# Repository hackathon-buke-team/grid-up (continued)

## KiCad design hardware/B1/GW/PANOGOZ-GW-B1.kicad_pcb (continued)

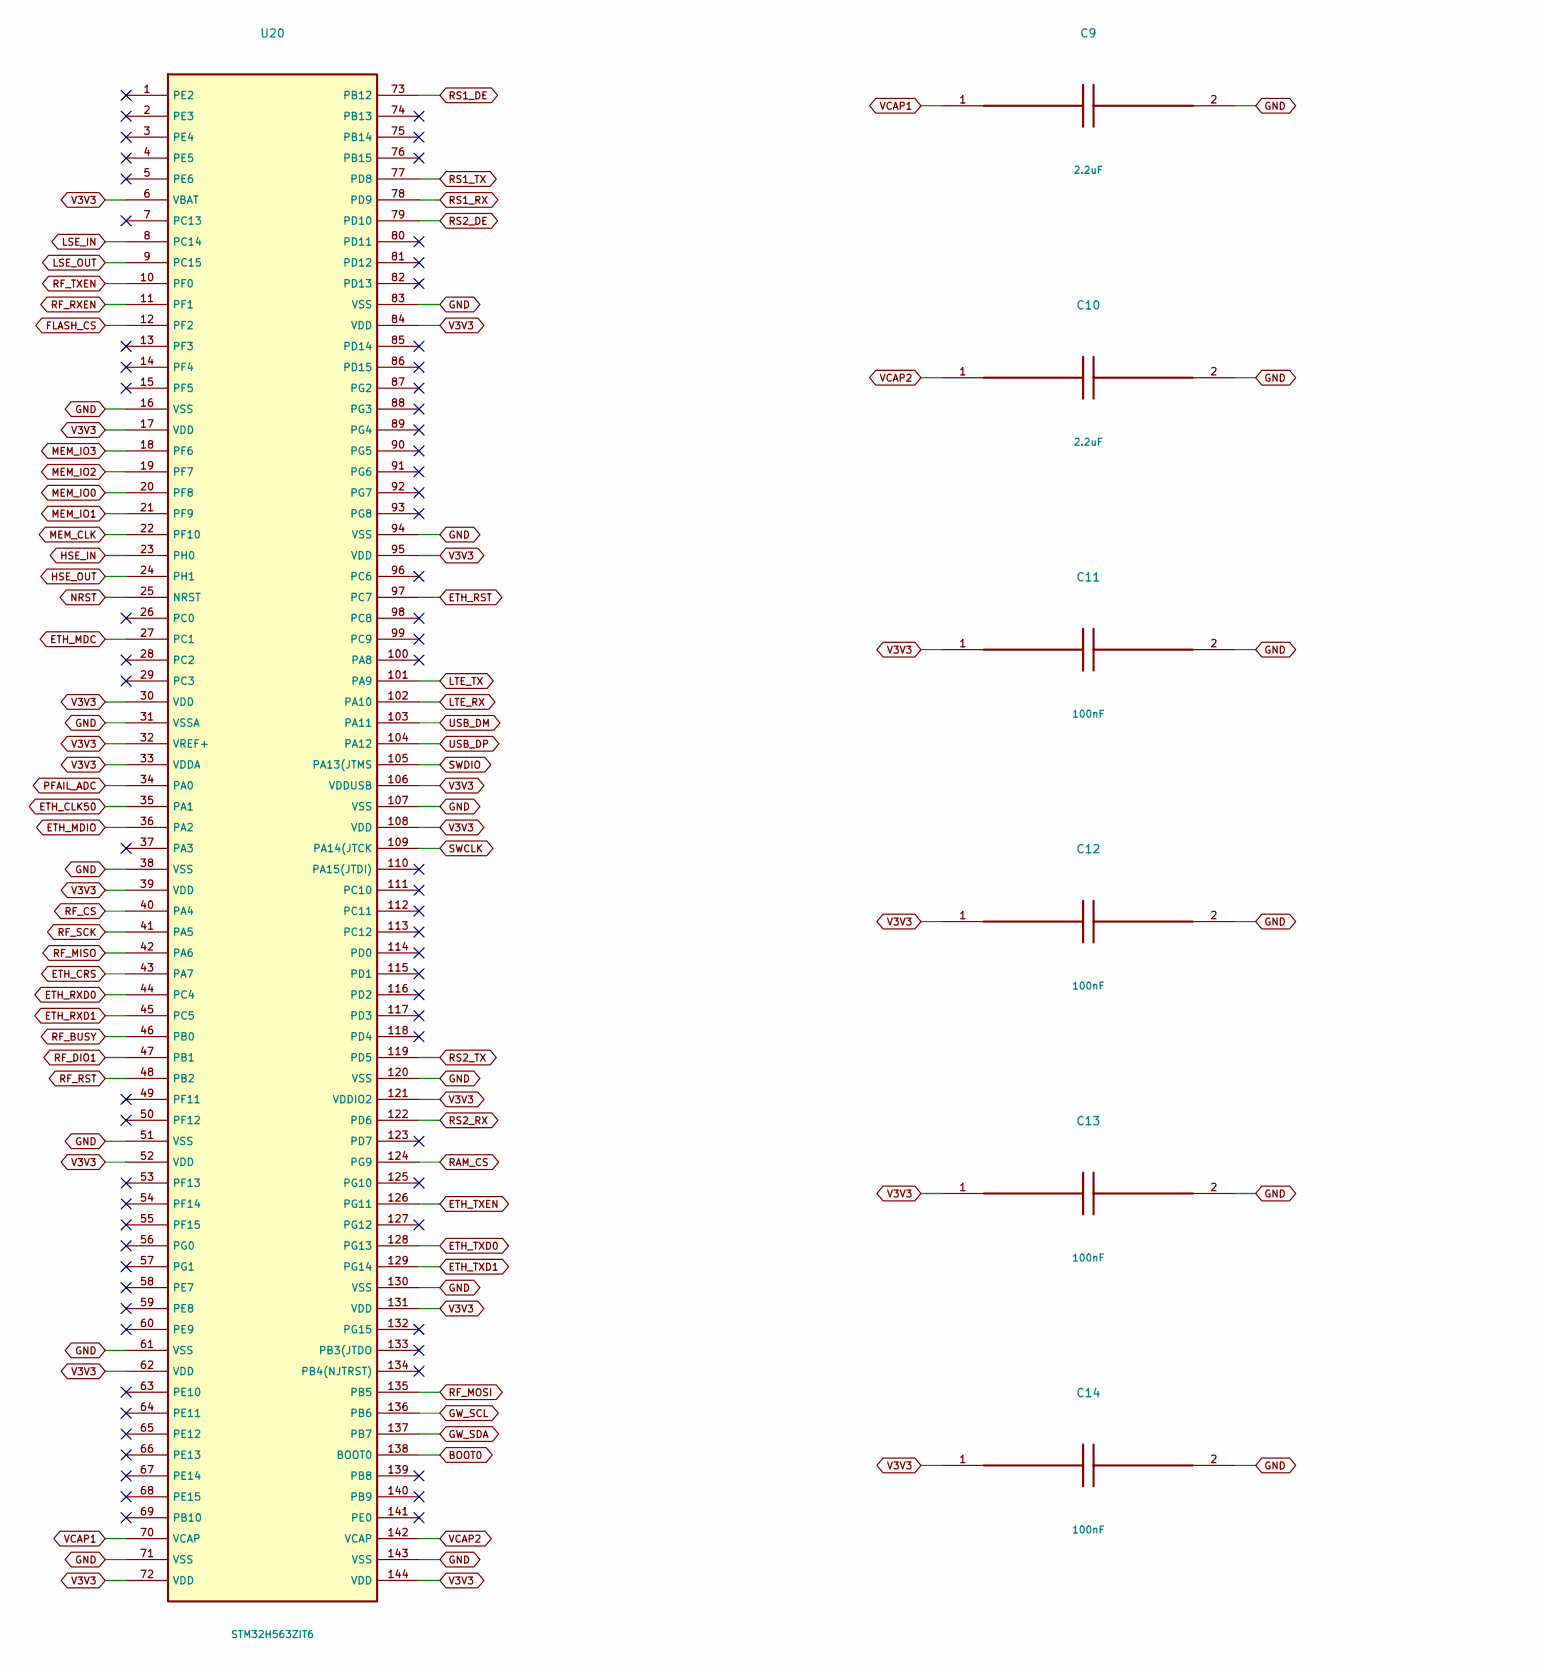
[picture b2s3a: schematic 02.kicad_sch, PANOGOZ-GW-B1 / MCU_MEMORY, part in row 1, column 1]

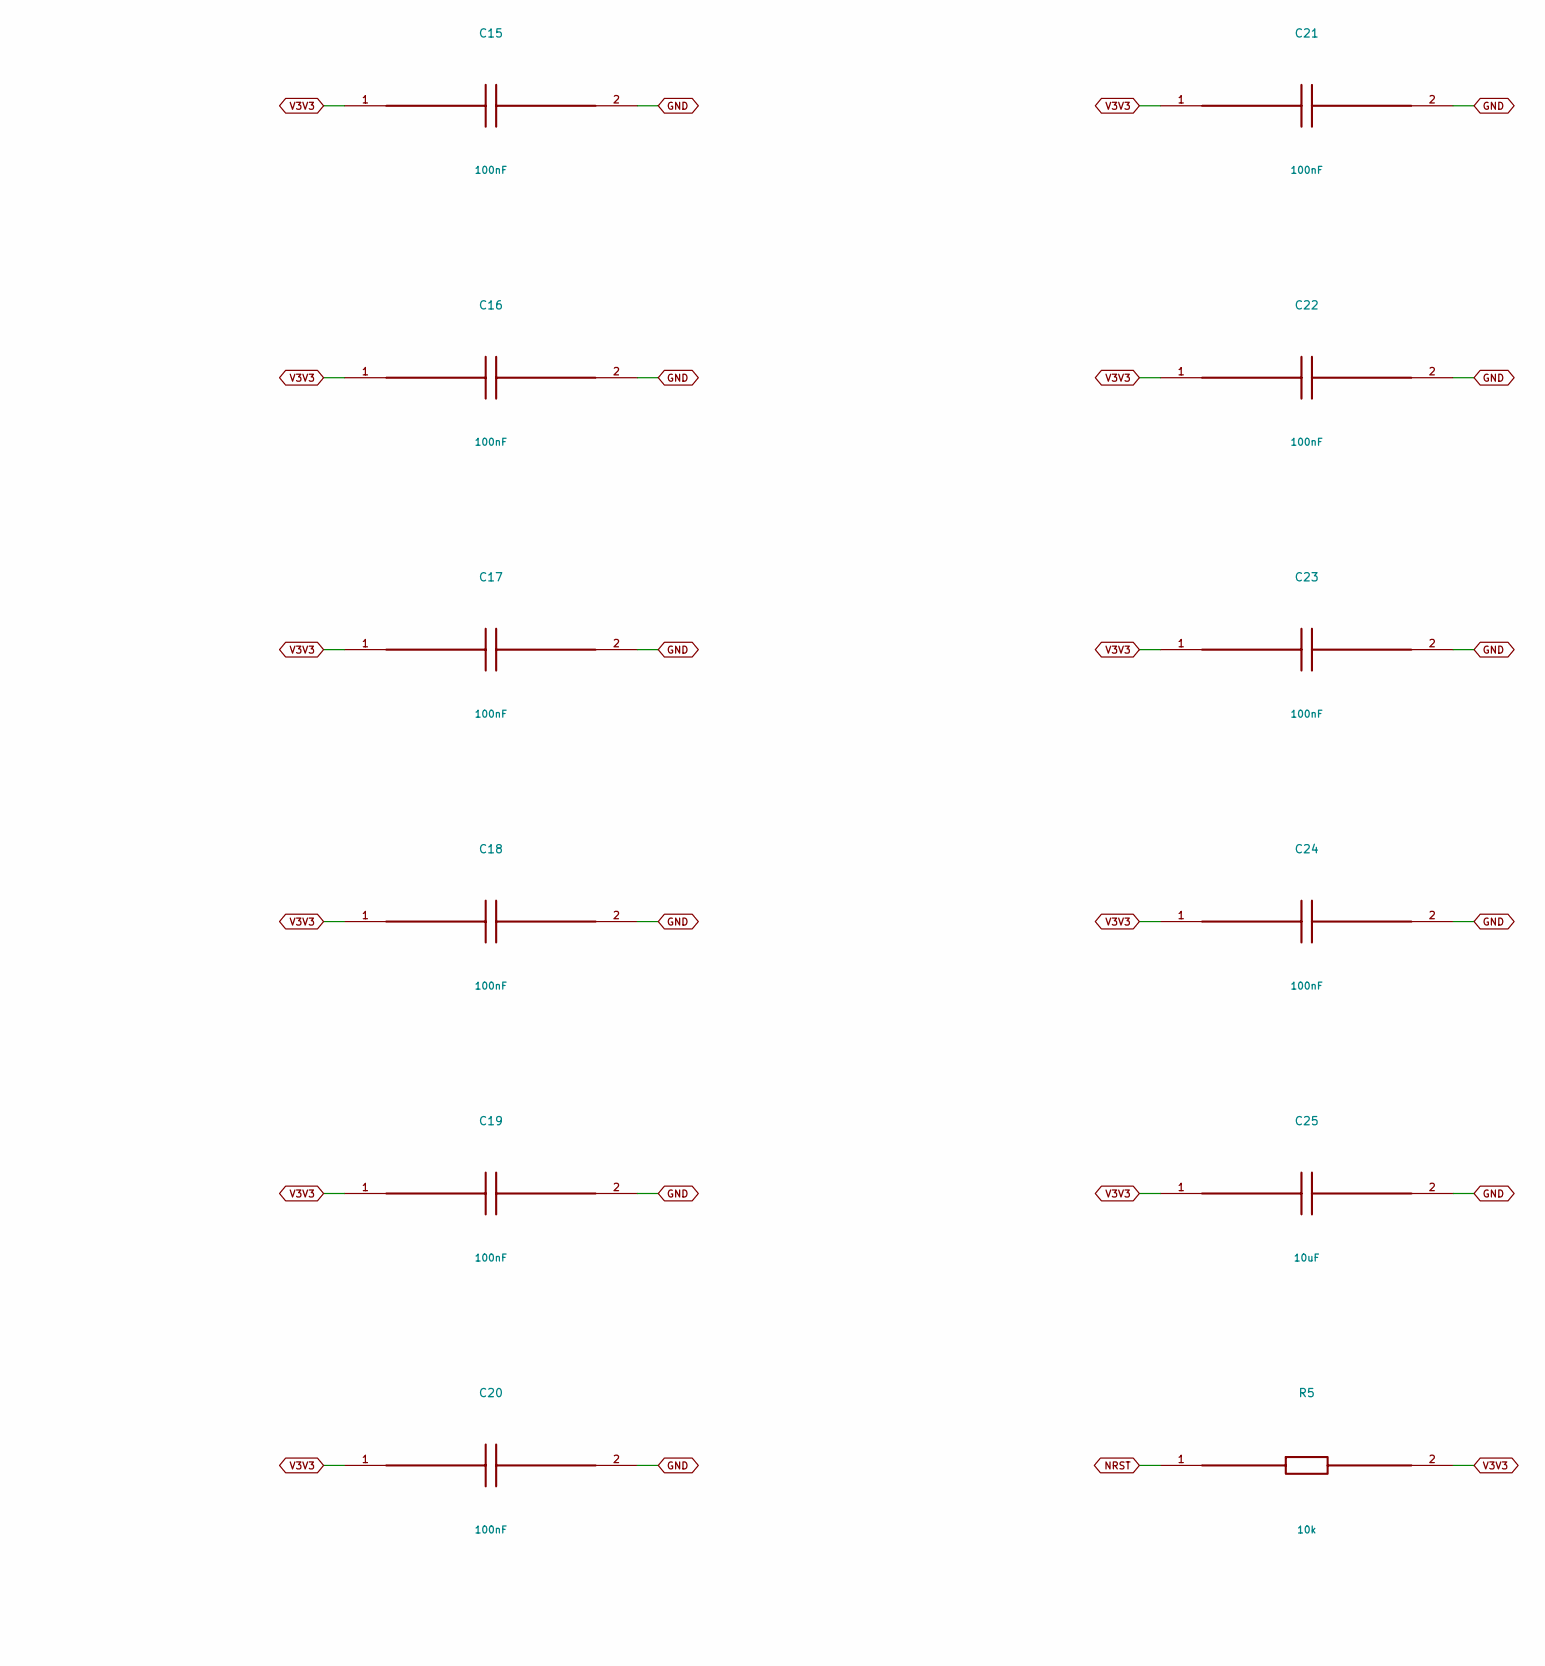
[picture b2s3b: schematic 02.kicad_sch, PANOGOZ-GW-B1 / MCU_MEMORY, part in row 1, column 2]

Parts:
C9, C10: 2.2uF; C_0402_1005Metric; MPN X7R 16V 2.2uF
C11, C12, C13, C14, C15, C16, C17, C18, C19, C20, C21, C22, C23, C24: 100nF; C_0402_1005Metric; MPN X7R 16V 100nF
C25: 10uF; C_0805_2012Metric; MPN X7R 16V 10uF
R5: 10k; R_0402_1005Metric; MPN 1% thick film 10k
U20: STM32H563ZIT6; LQFP-144_20x20mm_P0.5mm; MPN STM32H563ZIT6

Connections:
BOOT0: U20.138 (BOOT0); also elsewhere on the board
ETH_CLK50: U20.35 (PA1); also elsewhere on the board
ETH_CRS: U20.43 (PA7); also elsewhere on the board
ETH_MDC: U20.27 (PC1); also elsewhere on the board
ETH_MDIO: U20.36 (PA2); also elsewhere on the board
ETH_RST: U20.97 (PC7); also elsewhere on the board
ETH_RXD0: U20.44 (PC4); also elsewhere on the board
ETH_RXD1: U20.45 (PC5); also elsewhere on the board
ETH_TXD0: U20.128 (PG13); also elsewhere on the board
ETH_TXD1: U20.129 (PG14); also elsewhere on the board
ETH_TXEN: U20.126 (PG11); also elsewhere on the board
FLASH_CS: U20.12 (PF2); also elsewhere on the board
GND: C9.2, C10.2, C11.2, C12.2, C13.2, C14.2, C15.2, C16.2, C17.2, C18.2, C19.2, C20.2, C21.2, C22.2, C23.2, C24.2, C25.2, U20.16 (VSS), U20.31 (VSSA), U20.38 (VSS), U20.51 (VSS), U20.61 (VSS), U20.71 (VSS), U20.83 (VSS), U20.94 (VSS), U20.107 (VSS), U20.120 (VSS), U20.130 (VSS), U20.143 (VSS); also elsewhere on the board
GW_SCL: U20.136 (PB6); also elsewhere on the board
GW_SDA: U20.137 (PB7); also elsewhere on the board
HSE_IN: U20.23 (PH0); also elsewhere on the board
HSE_OUT: U20.24 (PH1); also elsewhere on the board
LSE_IN: U20.8 (PC14); also elsewhere on the board
LSE_OUT: U20.9 (PC15); also elsewhere on the board
LTE_RX: U20.102 (PA10); also elsewhere on the board
LTE_TX: U20.101 (PA9); also elsewhere on the board
MEM_CLK: U20.22 (PF10); also elsewhere on the board
MEM_IO0: U20.20 (PF8); also elsewhere on the board
MEM_IO1: U20.21 (PF9); also elsewhere on the board
MEM_IO2: U20.19 (PF7); also elsewhere on the board
MEM_IO3: U20.18 (PF6); also elsewhere on the board
NRST: R5.1, U20.25 (NRST); also elsewhere on the board
PFAIL_ADC: U20.34 (PA0); also elsewhere on the board
RAM_CS: U20.124 (PG9); also elsewhere on the board
RF_BUSY: U20.46 (PB0); also elsewhere on the board
RF_CS: U20.40 (PA4); also elsewhere on the board
RF_DIO1: U20.47 (PB1); also elsewhere on the board
RF_MISO: U20.42 (PA6); also elsewhere on the board
RF_MOSI: U20.135 (PB5); also elsewhere on the board
RF_RST: U20.48 (PB2); also elsewhere on the board
RF_RXEN: U20.11 (PF1); also elsewhere on the board
RF_SCK: U20.41 (PA5); also elsewhere on the board
RF_TXEN: U20.10 (PF0); also elsewhere on the board
RS1_DE: U20.73 (PB12); also elsewhere on the board
RS1_RX: U20.78 (PD9); also elsewhere on the board
RS1_TX: U20.77 (PD8); also elsewhere on the board
RS2_DE: U20.79 (PD10); also elsewhere on the board
RS2_RX: U20.122 (PD6); also elsewhere on the board
RS2_TX: U20.119 (PD5); also elsewhere on the board
SWCLK: U20.109 (PA14(JTCK); also elsewhere on the board
SWDIO: U20.105 (PA13(JTMS); also elsewhere on the board
USB_DM: U20.103 (PA11); also elsewhere on the board
USB_DP: U20.104 (PA12); also elsewhere on the board
V3V3: C11.1, C12.1, C13.1, C14.1, C15.1, C16.1, C17.1, C18.1, C19.1, C20.1, C21.1, C22.1, C23.1, C24.1, C25.1, R5.2, U20.6 (VBAT), U20.17 (VDD), U20.30 (VDD), U20.32 (VREF+), U20.33 (VDDA), U20.39 (VDD), U20.52 (VDD), U20.62 (VDD), U20.72 (VDD), U20.84 (VDD), U20.95 (VDD), U20.106 (VDDUSB), U20.108 (VDD), U20.121 (VDDIO2), U20.131 (VDD), U20.144 (VDD); also elsewhere on the board
VCAP1: C9.1, U20.70 (VCAP)
VCAP2: C10.1, U20.142 (VCAP)

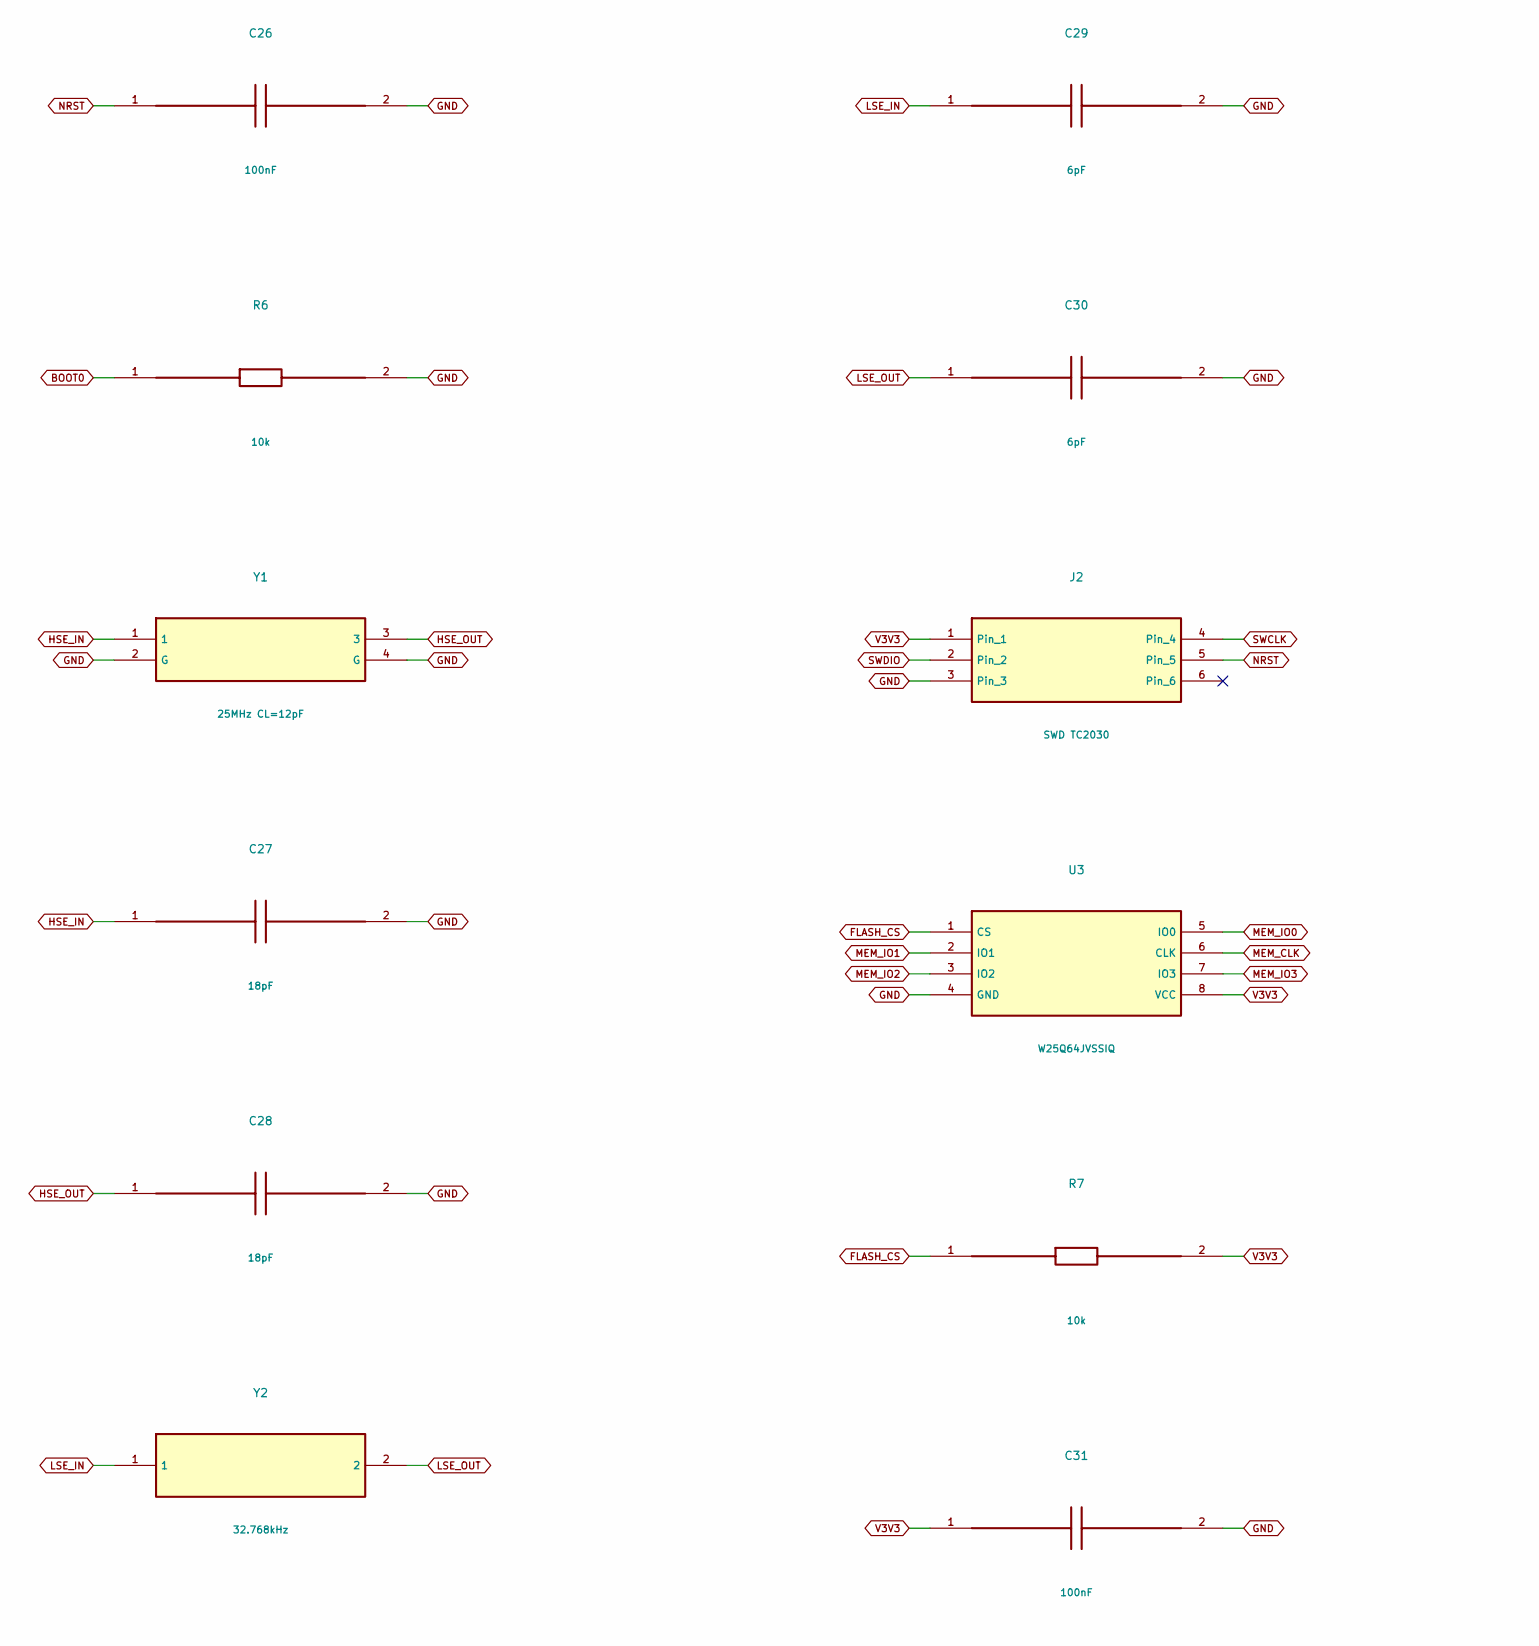
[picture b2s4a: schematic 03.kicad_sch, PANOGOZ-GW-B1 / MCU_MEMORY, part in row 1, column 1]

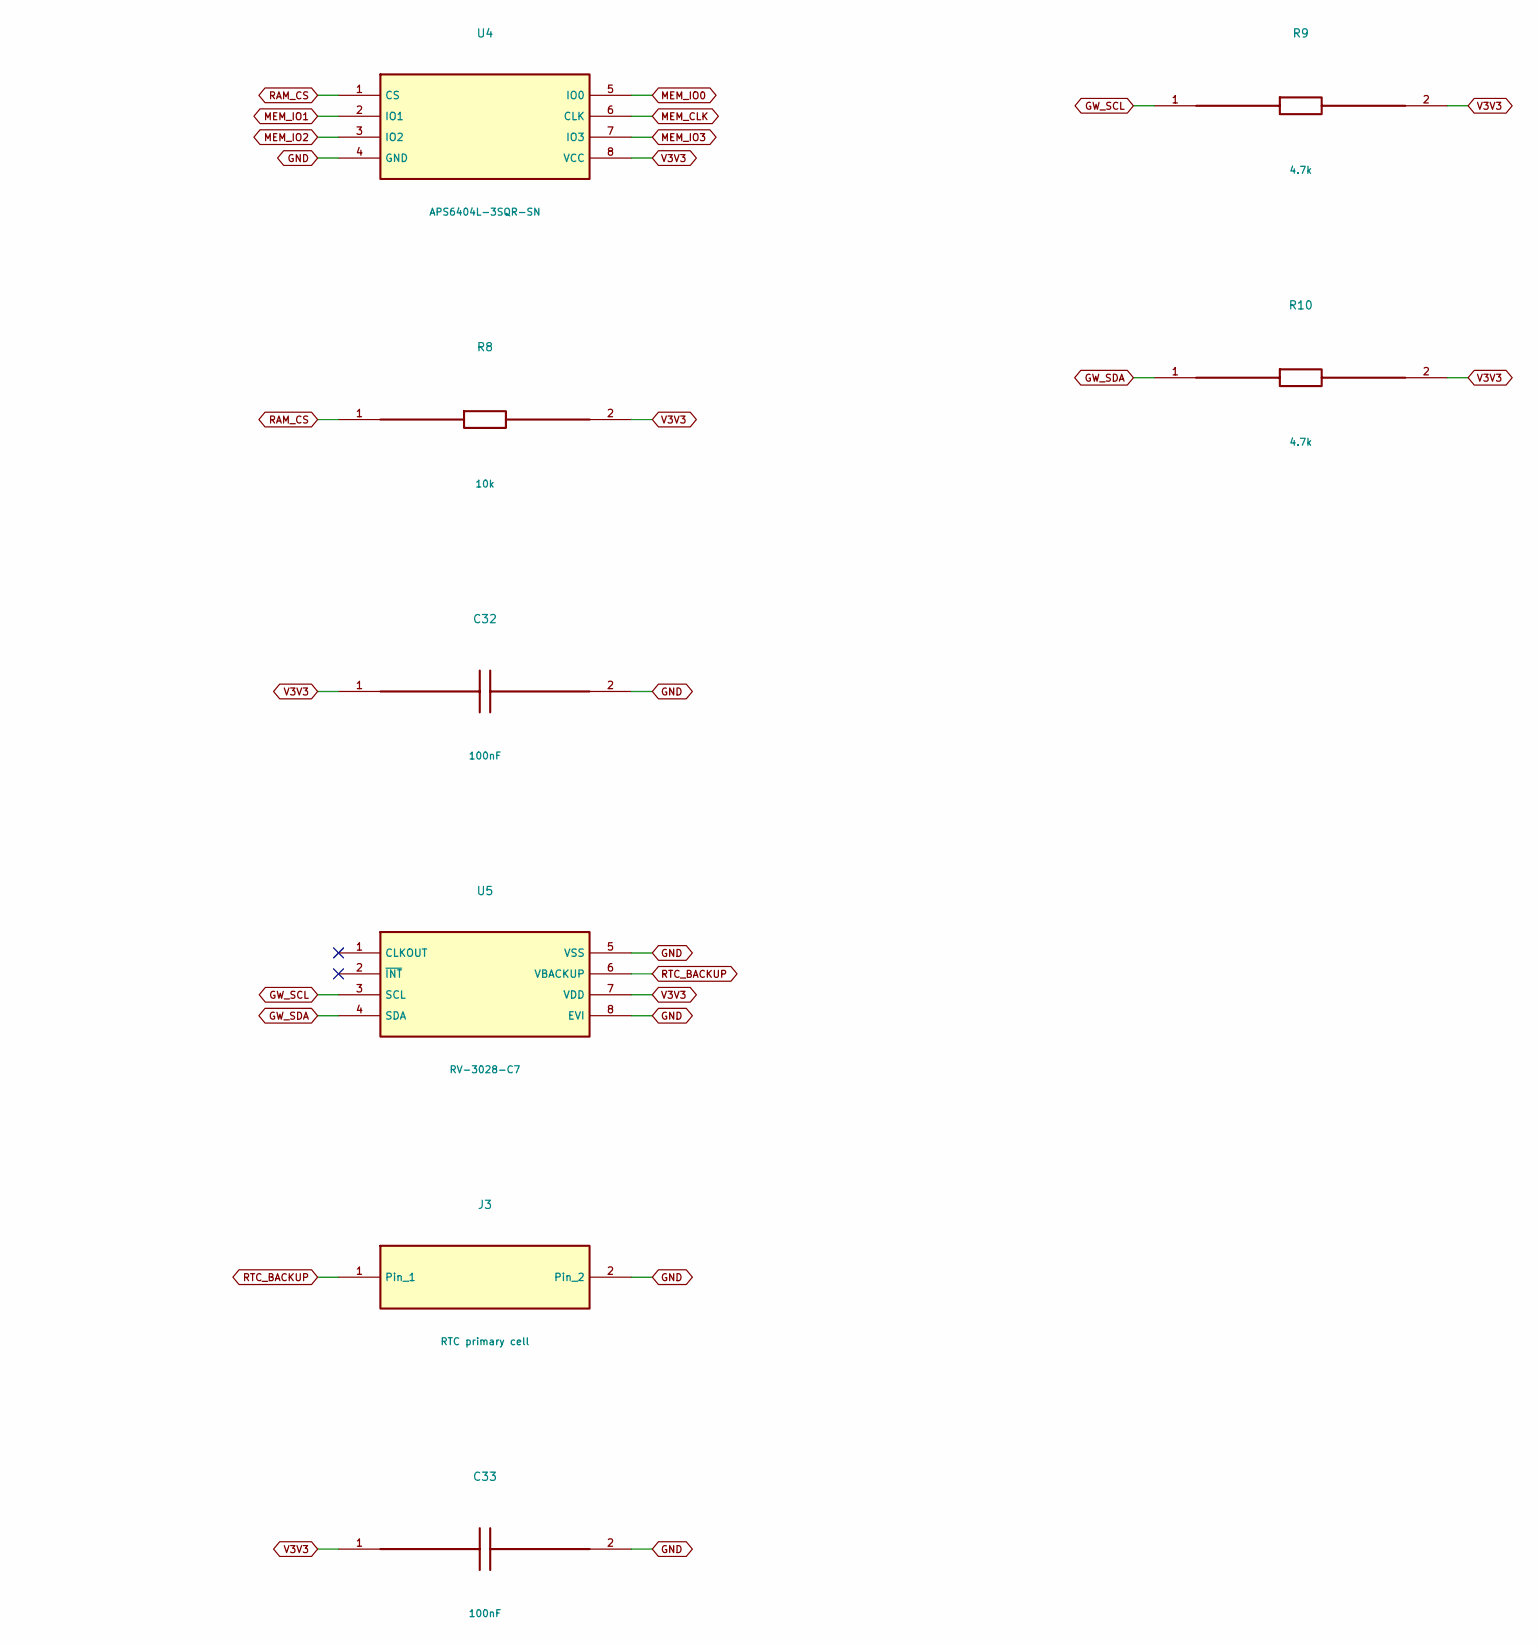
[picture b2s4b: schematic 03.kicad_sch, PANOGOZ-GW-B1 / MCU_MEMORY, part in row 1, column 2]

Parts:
C26, C31, C32, C33: 100nF; C_0402_1005Metric; MPN X7R 16V 100nF
C27, C28: 18pF; C_0402_1005Metric; MPN X7R 16V 18pF
C29, C30: 6pF; C_0402_1005Metric; MPN X7R 16V 6pF
J2: SWD TC2030; Tag-Connect_TC2030-IDC-NL_2x03_P1.27mm_Vertical; MPN SWD TC2030
J3: RTC primary cell; JST_SH_SM02B-SRSS-TB_1x02-1MP_P1.00mm_Horizontal; MPN RTC primary cell
R6, R7, R8: 10k; R_0402_1005Metric; MPN 1% thick film 10k
R9, R10: 4.7k; R_0402_1005Metric; MPN 1% thick film 4.7k
U3: W25Q64JVSSIQ; SOIC-8_3.9x4.9mm_P1.27mm; MPN W25Q64JVSSIQ
U4: APS6404L-3SQR-SN; SOIC-8_3.9x4.9mm_P1.27mm; MPN APS6404L-3SQR-SN
U5: RV-3028-C7; MicroCrystal_C7_SON-8_1.5x3.2mm_P0.9mm; MPN RV-3028-C7
Y1: 25MHz CL=12pF; Crystal_SMD_3225-4Pin_3.2x2.5mm; MPN 25MHz CL=12pF
Y2: 32.768kHz; Crystal_SMD_3215-2Pin_3.2x1.5mm; MPN 32.768kHz

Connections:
BOOT0: R6.1; also elsewhere on the board
FLASH_CS: R7.1, U3.1 (CS); also elsewhere on the board
GND: C26.2, C27.2, C28.2, C29.2, C30.2, C31.2, C32.2, C33.2, J2.3, J3.2, R6.2, U3.4 (GND), U4.4 (GND), U5.5 (VSS), U5.8 (EVI), Y1.2 (G), Y1.4 (G); also elsewhere on the board
GW_SCL: R9.1, U5.3 (SCL); also elsewhere on the board
GW_SDA: R10.1, U5.4 (SDA); also elsewhere on the board
HSE_IN: C27.1, Y1.1; also elsewhere on the board
HSE_OUT: C28.1, Y1.3; also elsewhere on the board
LSE_IN: C29.1, Y2.1; also elsewhere on the board
LSE_OUT: C30.1, Y2.2; also elsewhere on the board
MEM_CLK: U3.6 (CLK), U4.6 (CLK); also elsewhere on the board
MEM_IO0: U3.5 (IO0), U4.5 (IO0); also elsewhere on the board
MEM_IO1: U3.2 (IO1), U4.2 (IO1); also elsewhere on the board
MEM_IO2: U3.3 (IO2), U4.3 (IO2); also elsewhere on the board
MEM_IO3: U3.7 (IO3), U4.7 (IO3); also elsewhere on the board
NRST: C26.1, J2.5; also elsewhere on the board
RAM_CS: R8.1, U4.1 (CS); also elsewhere on the board
RTC_BACKUP: J3.1, U5.6 (VBACKUP)
SWCLK: J2.4; also elsewhere on the board
SWDIO: J2.2; also elsewhere on the board
V3V3: C31.1, C32.1, C33.1, J2.1, R7.2, R8.2, R9.2, R10.2, U3.8 (VCC), U4.8 (VCC), U5.7 (VDD); also elsewhere on the board

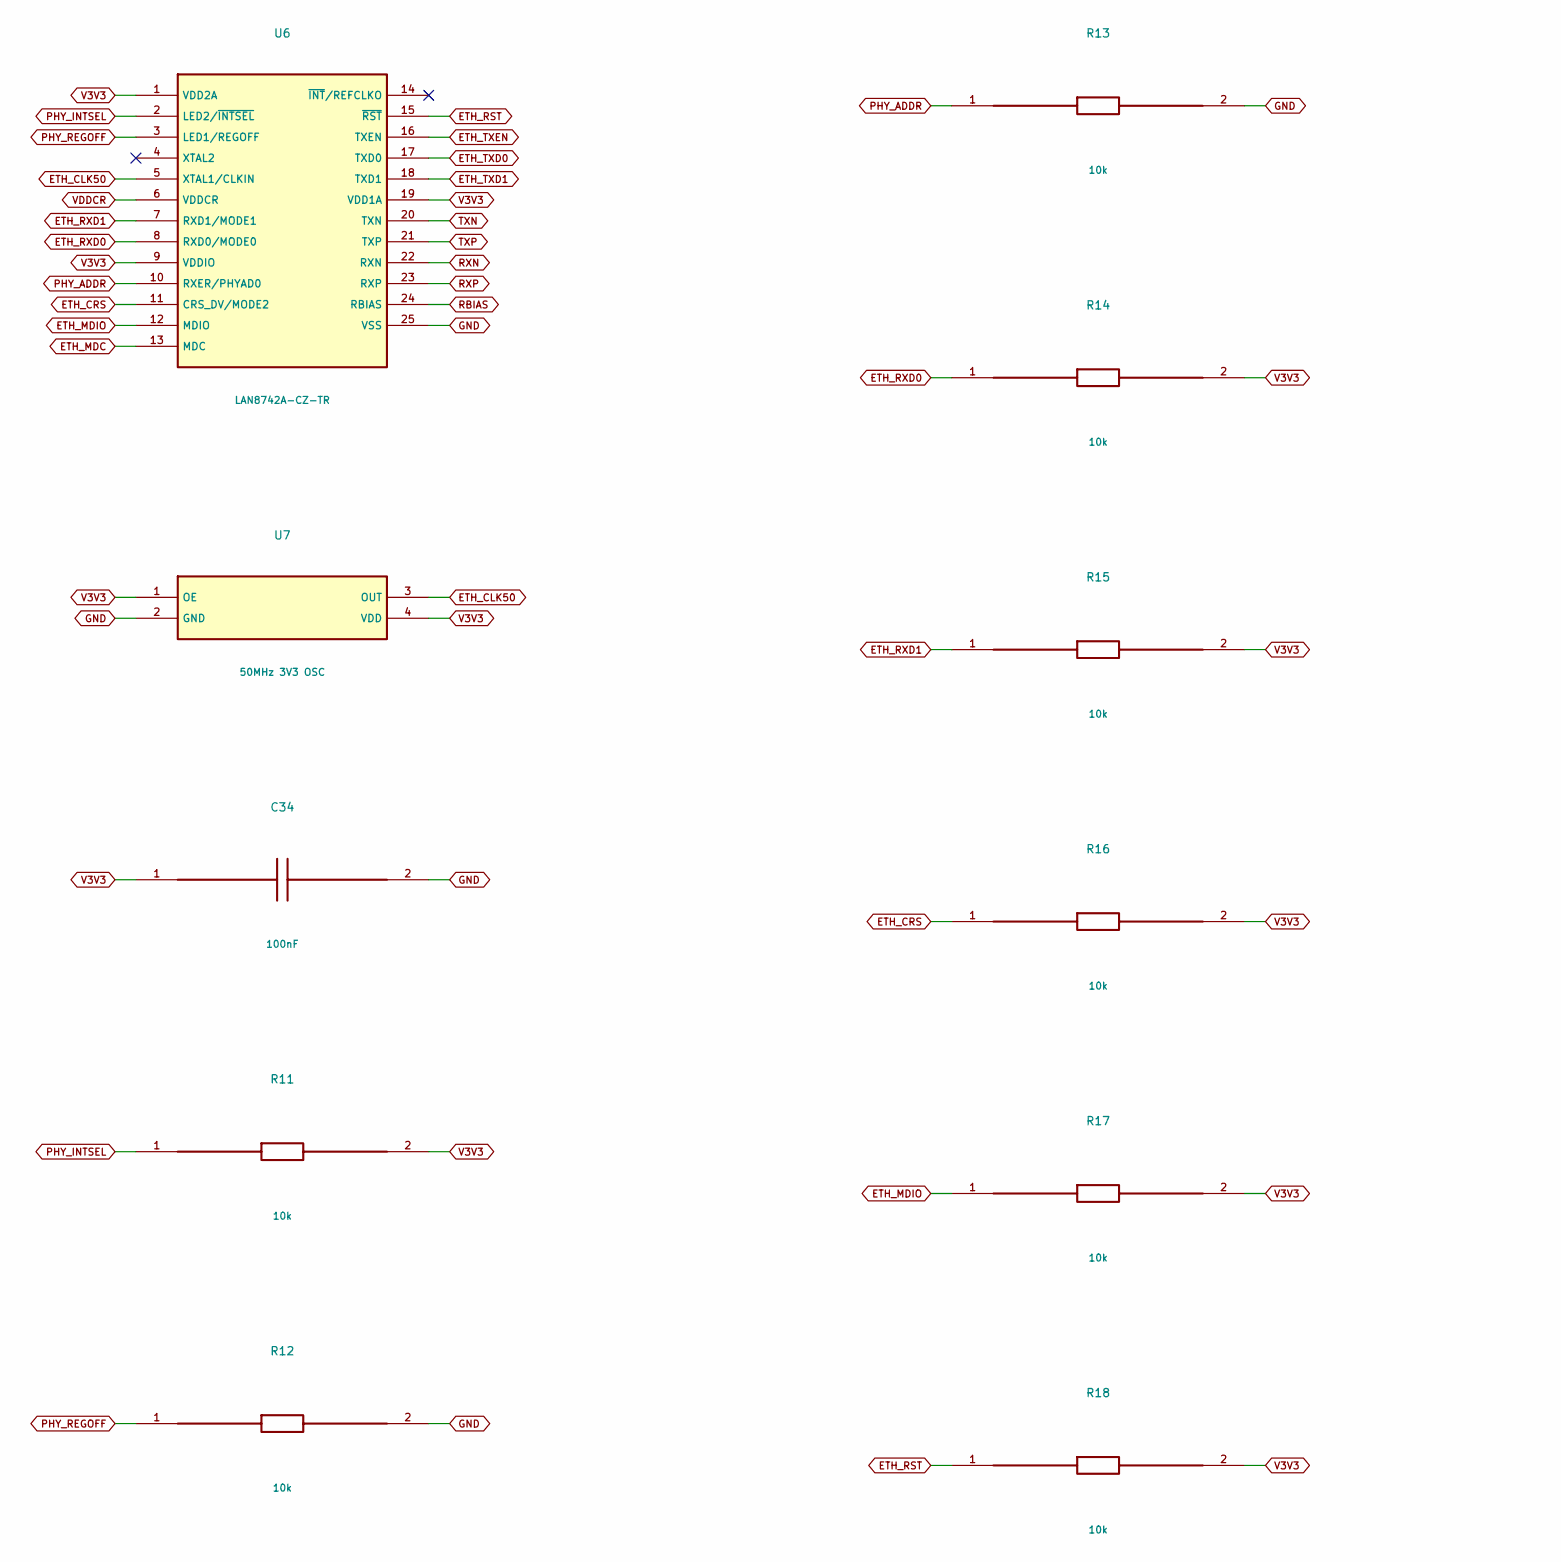
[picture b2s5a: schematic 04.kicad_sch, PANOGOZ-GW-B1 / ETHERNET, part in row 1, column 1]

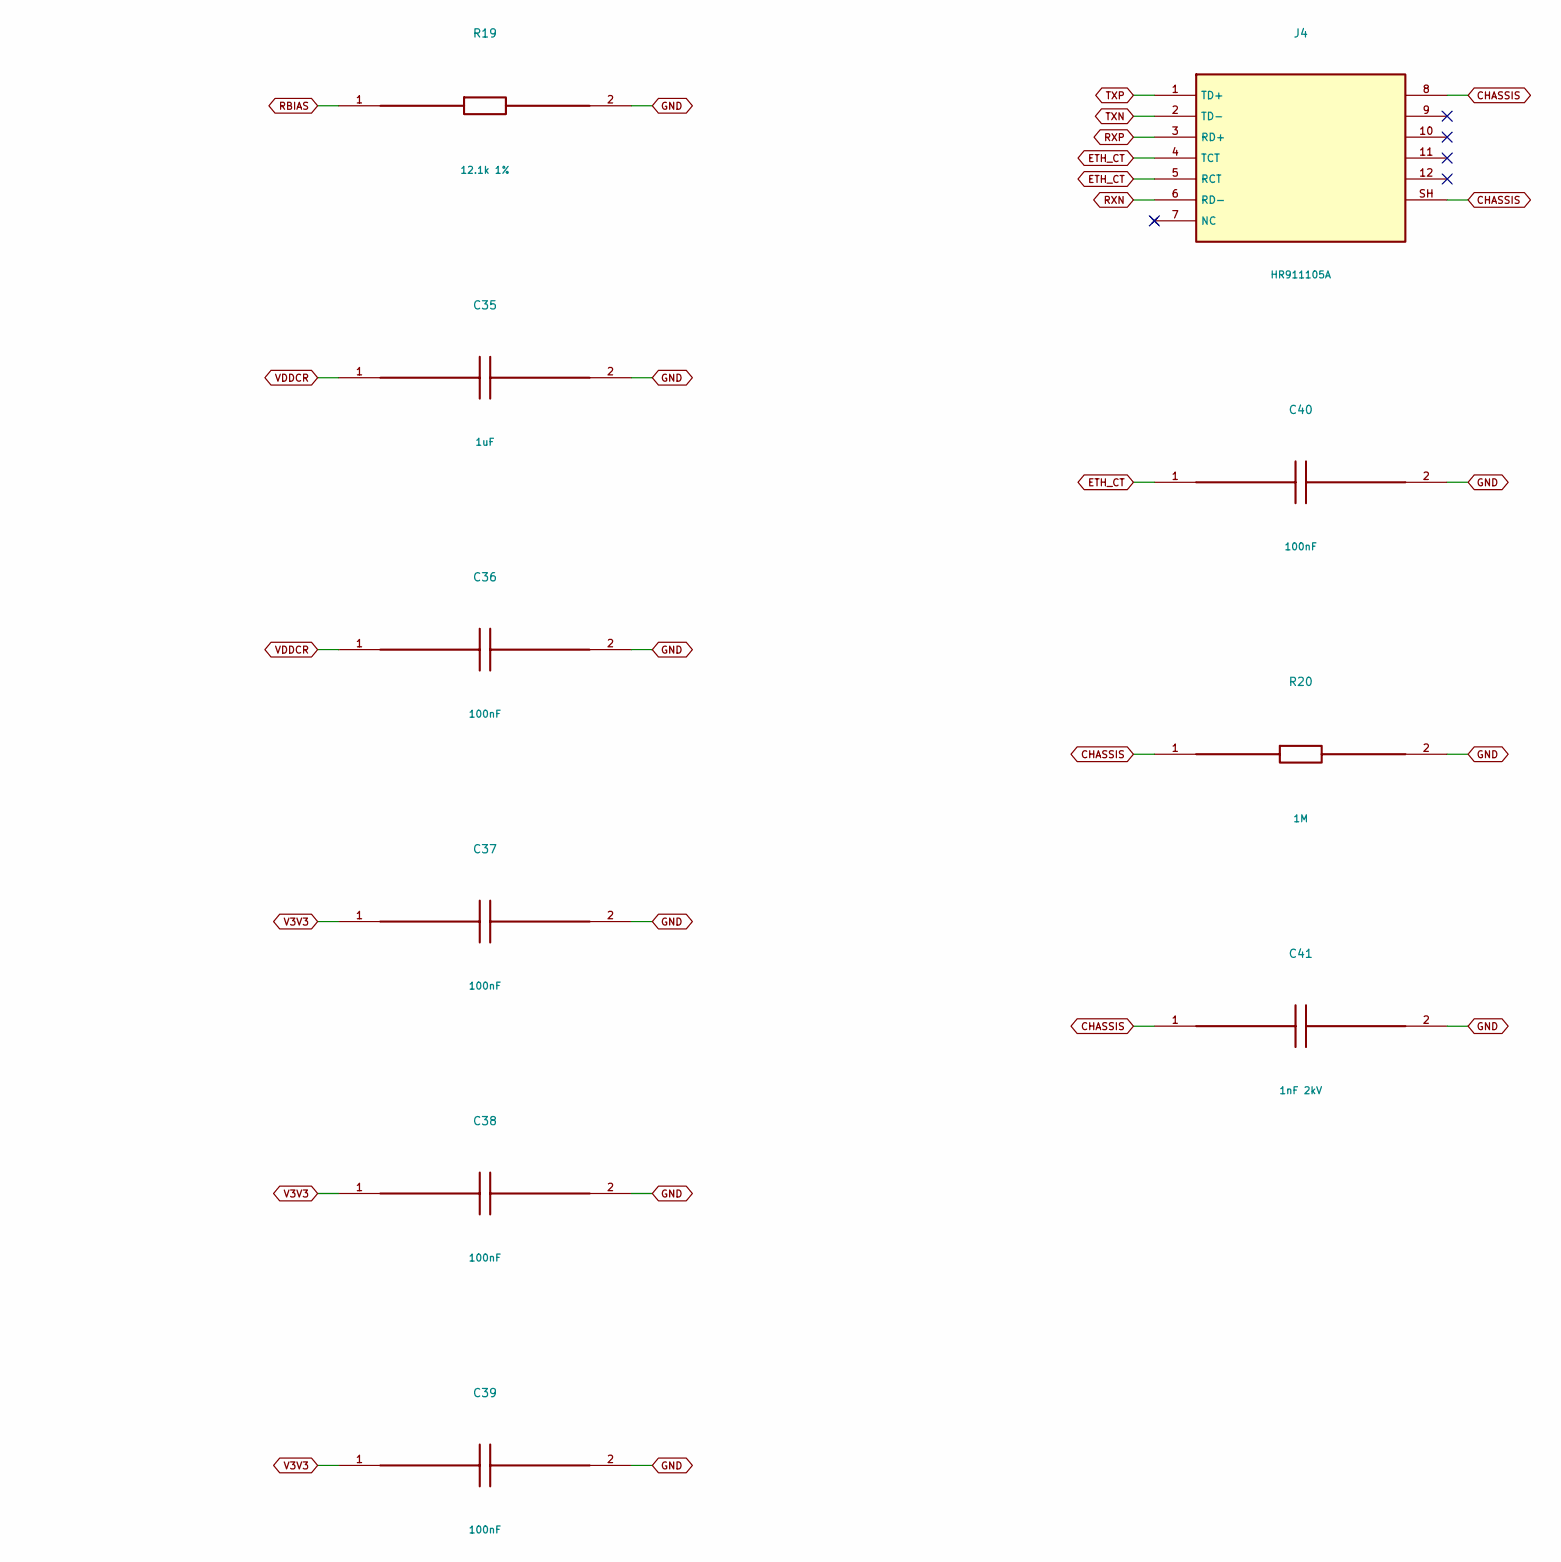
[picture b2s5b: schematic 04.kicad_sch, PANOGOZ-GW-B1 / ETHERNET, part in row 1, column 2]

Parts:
C34, C36, C37, C38, C39, C40: 100nF; C_0402_1005Metric; MPN X7R 16V 100nF
C35: 1uF; C_0402_1005Metric; MPN X7R 16V 1uF
C41: 1nF 2kV; C_1206_3216Metric; MPN X7R 16V 1nF 2kV
J4: HR911105A; RJ45_Hanrun_HR911105A_Horizontal; MPN HR911105A
R11, R12, R13, R14, R15, R16, R17, R18: 10k; R_0402_1005Metric; MPN 1% thick film 10k
R19: 12.1k 1%; R_0402_1005Metric; MPN 1% thick film 12.1k 1%
R20: 1M; R_0402_1005Metric; MPN 1% thick film 1M
U6: LAN8742A-CZ-TR; VQFN-24-1EP_4x4mm_P0.5mm_EP2.5x2.5mm_ThermalVias; MPN LAN8742A-CZ-TR
U7: 50MHz 3V3 OSC; Oscillator_SMD_Abracon_ASE-4Pin_3.2x2.5mm; MPN 50MHz 3V3 OSC

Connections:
CHASSIS: C41.1, J4.8, J4.SH, R20.1
ETH_CLK50: U6.5 (XTAL1/CLKIN), U7.3 (OUT); also elsewhere on the board
ETH_CRS: R16.1, U6.11 (CRS_DV/MODE2); also elsewhere on the board
ETH_CT: C40.1, J4.4 (TCT), J4.5 (RCT)
ETH_MDC: U6.13 (MDC); also elsewhere on the board
ETH_MDIO: R17.1, U6.12 (MDIO); also elsewhere on the board
ETH_RST: R18.1, U6.15 (~RST); also elsewhere on the board
ETH_RXD0: R14.1, U6.8 (RXD0/MODE0); also elsewhere on the board
ETH_RXD1: R15.1, U6.7 (RXD1/MODE1); also elsewhere on the board
ETH_TXD0: U6.17 (TXD0); also elsewhere on the board
ETH_TXD1: U6.18 (TXD1); also elsewhere on the board
ETH_TXEN: U6.16 (TXEN); also elsewhere on the board
GND: C34.2, C35.2, C36.2, C37.2, C38.2, C39.2, C40.2, C41.2, R12.2, R13.2, R19.2, R20.2, U6.25 (VSS), U7.2 (GND); also elsewhere on the board
PHY_ADDR: R13.1, U6.10 (RXER/PHYAD0)
PHY_INTSEL: R11.1, U6.2 (LED2/~INTSEL)
PHY_REGOFF: R12.1, U6.3 (LED1/REGOFF)
RBIAS: R19.1, U6.24 (RBIAS)
RXN: J4.6 (RD-), U6.22 (RXN)
RXP: J4.3 (RD+), U6.23 (RXP)
TXN: J4.2 (TD-), U6.20 (TXN)
TXP: J4.1 (TD+), U6.21 (TXP)
V3V3: C34.1, C37.1, C38.1, C39.1, R11.2, R14.2, R15.2, R16.2, R17.2, R18.2, U6.1 (VDD2A), U6.9 (VDDIO), U6.19 (VDD1A), U7.1 (OE), U7.4 (VDD); also elsewhere on the board
VDDCR: C35.1, C36.1, U6.6 (VDDCR)
